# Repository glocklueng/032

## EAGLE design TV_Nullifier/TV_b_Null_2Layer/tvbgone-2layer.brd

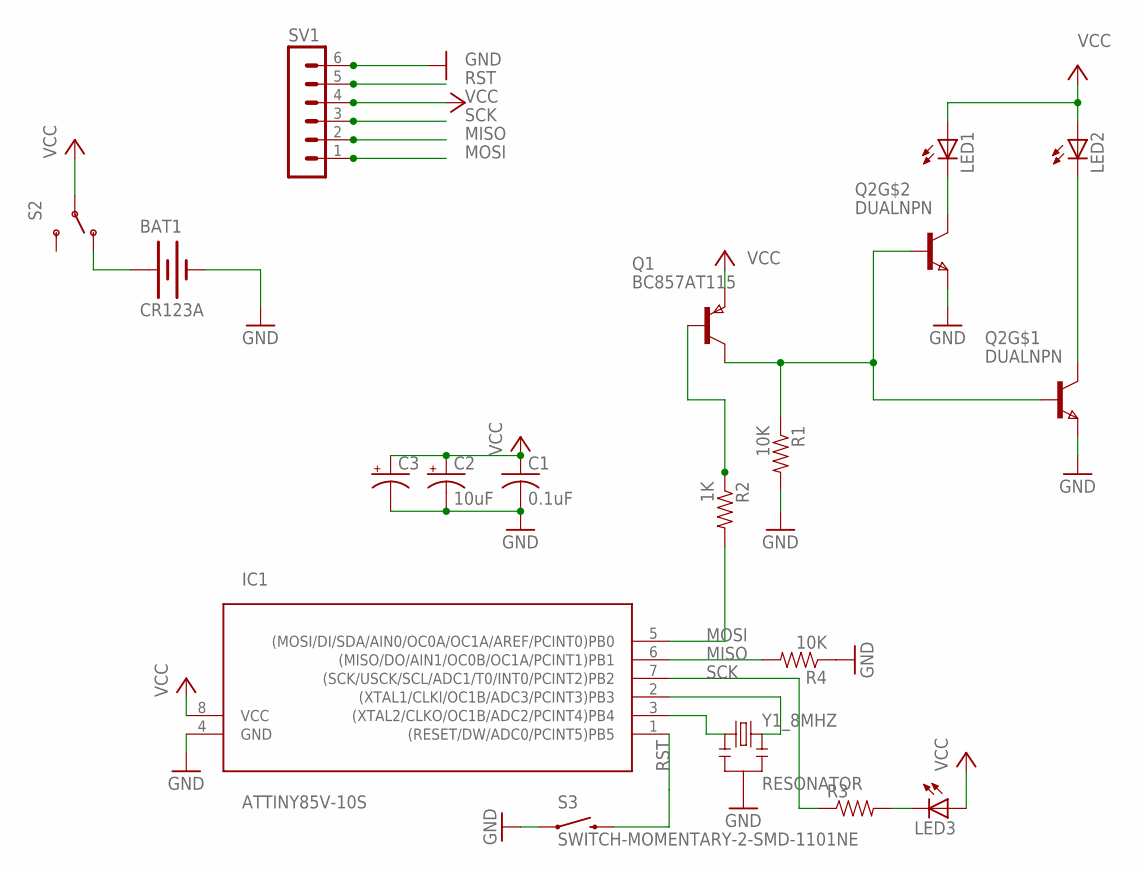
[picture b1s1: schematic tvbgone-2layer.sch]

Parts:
BAT1: CR123A; TVBGONE-ADJ_BATTERY_CR123A
C1: 0.1uF; C0603K
C2: 10uF; EIA3216
C3: SPARKFUN_CAP_POL3528; SPARKFUN_EIA3528
IC1: ATTINY85V-10S; SOIC8
LED1, LED2: TVBGONE3_LEDSIDEIR; TVBGONE3_SIDE_IR_NSL
LED3: LEDCHIPLED_0603; CHIPLED_0603
Q1: BC857AT115; SOT416
Q2: DUALNPN; SSOT6
R1, R4: 10K; 0805
R2, R3: 1K; 0805
S2: SWITCH-SPDT-SMD-A; SWITCH-SPST-SMD-A
S3: SWITCH-MOMENTARY-2-SMD-1101NE; TACTILE-SWITCH-1101NE
SV1: CON-LSTB_MA06-1
Y1_8MHZ: RESONATOR; SPARKFUN_RESONATOR-SMD

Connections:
GND: BAT1.-, C1.2, C2.C (-), C3.C (-), IC1.4 (GND), Q2.2 (E), Q2.5 (E), R1.2, R4.1, S3.P$1 (1), SV1.6, Y1_8MHZ.2
MISO: IC1.6 ((MISO/DO/AIN1/OC0B/OC1A/PCINT1)PB1), R4.2, SV1.2
MOSI: IC1.5 ((MOSI/DI/SDA/AIN0/OC0A/OC1A/AREF/PCINT0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), R2.2, SV1.1
unnamed: IC1.3 ((XTAL2/CLKO/OC1B/ADC2/PCINT4)PB4), Y1_8MHZ.1
unnamed: IC1.2 ((XTAL1/CLKI/OC1B/ADC3/PCINT3)PB3), Y1_8MHZ.3
unnamed: LED3.C, R3.2
unnamed: LED1.C, Q2.4 (C)
unnamed: LED2.C, Q2.6 (C)
unnamed: Q1.2 (B), R2.1
unnamed: BAT1.+, S2.1 (O)
unnamed: Q1.1 (C), Q2.1 (B), Q2.3 (B), R1.1
RST: IC1.1 ((RESET/DW/ADC0/PCINT5)PB5), S3.P$2 (2), SV1.5
SCK: IC1.7 ((SCK/USCK/SCL/ADC1/T0/INT0/PCINT2)PB2), R3.1, SV1.3
VCC: C1.1, C2.A (+), C3.A (+), IC1.8 (VCC), LED1.A, LED2.A, LED3.A, Q1.3 (E), S2.2, SV1.4

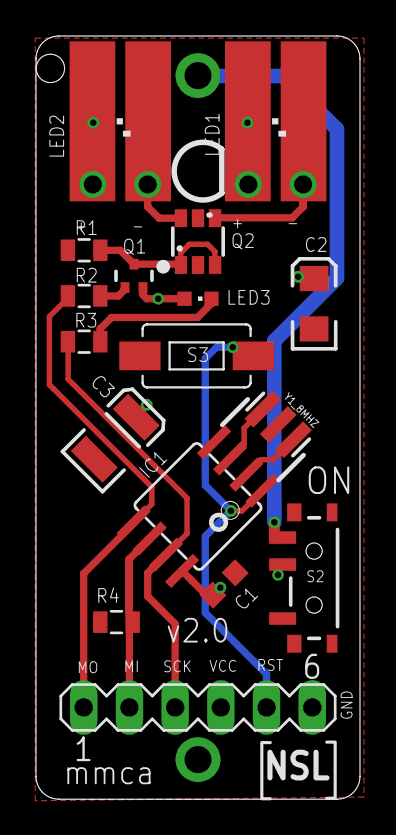
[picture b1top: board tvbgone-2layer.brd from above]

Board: 2 copper layers, 18.0 x 42.4 mm, 18 parts (0 on the bottom side), 14 nets.

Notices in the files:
parts and their libraries:
SparkFun-Electromechanical: Licensing: CC v3.0 Share-Alike You are welcome to use this library for commercial purposes.
